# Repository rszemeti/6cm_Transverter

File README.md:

# 6cm_Transverter
Transverter for the 6cm band

Filters done in Sonnet Lite
PCB In Eagle

RF Board is setup for Rogers RO4003C, 0.508mm
DC Board is any FR4

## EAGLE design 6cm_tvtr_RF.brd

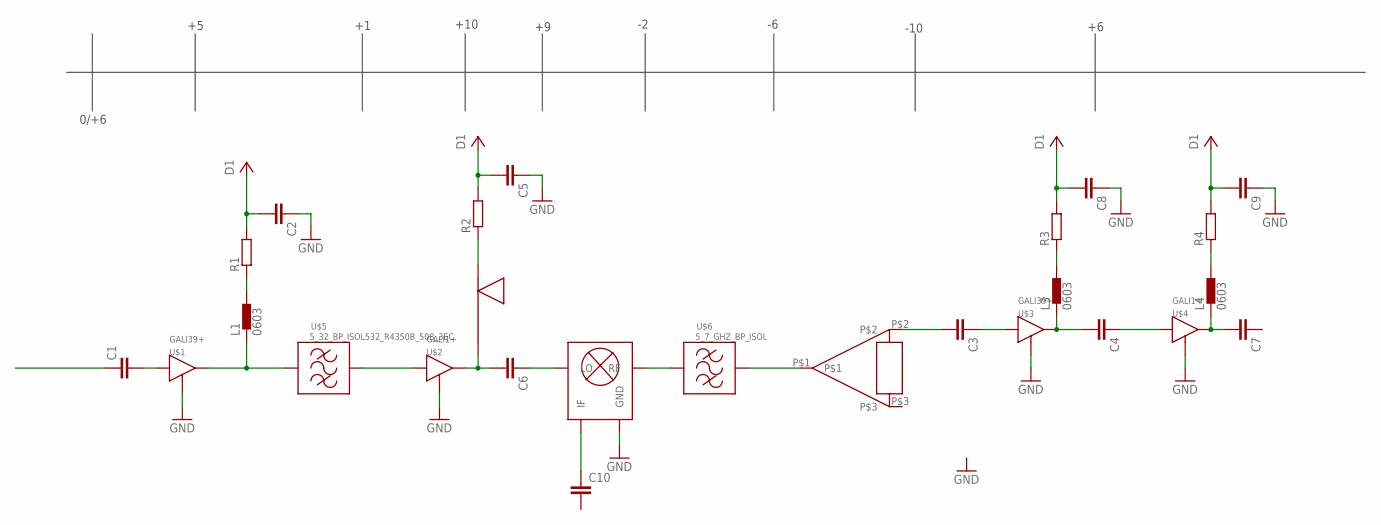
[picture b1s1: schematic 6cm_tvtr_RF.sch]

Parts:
C1, C2, C3, C4, C5, C6, C7, C8, C9, C10: C-EUC0603K; C0603K
L1, L3, L4: 0603
R1, R2, R3, R4: R-EU_R0603; R0603
U$1, U$3: GALI39+; DF782
U$2, U$4: GALI1+; DF782
U$5: 5_32_BP_ISOL532_R4350B_508_3EC; 532_R4350B_508_3EC
U$6: 5_7_GHZ_BP_ISOL; 576_R403C_508_5TH
U$7: 576_WILK
U$8: MDB-73H+; DG1847
U$9: STUB; 5.3_R4350B_508_STUB_90

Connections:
D1: C5.2, C8.2, C9.2, R2.2, R3.2, R4.2
GND: C2.1, C5.1, C8.1, C9.1, U$1.P$2 (GND), U$1.P$4 (GND), U$1.P$5 (GND), U$1.P$6 (GND), U$1.P$7 (GND), U$1.P$8 (GND), U$2.P$2 (GND), U$2.P$4 (GND), U$2.P$5 (GND), U$2.P$6 (GND), U$2.P$7 (GND), U$2.P$8 (GND), U$3.P$2 (GND), U$3.P$4 (GND), U$3.P$5 (GND), U$3.P$6 (GND), U$3.P$7 (GND), U$3.P$8 (GND), U$4.P$2 (GND), U$4.P$4 (GND), U$4.P$5 (GND), U$4.P$6 (GND), U$4.P$7 (GND), U$4.P$8 (GND), U$8.P$2 (GND), U$8.P$4 (GND), U$8.P$8 (GND), U$8.P$10 (GND), U$8.P$15 (GND), U$8.P$17 (GND), U$8.PAD1 (GND), U$8.PAD2 (GND), U$8.PAD3 (GND), U$8.PAD4 (GND)
unnamed: C1.2, U$1.P$1 (IN)
unnamed: R2.1, U$9.DC
unnamed: C6.2, U$2.P$3 (OUT), U$9.RF (RF_END)
unnamed: L1.P$2 (2), R1.1
unnamed: L1.P$1 (1), U$1.P$3 (OUT), U$5.P$1
unnamed: U$2.P$1 (IN), U$5.P$2
unnamed: U$6.P$2, U$7.P$1
unnamed: C6.1, U$8.P$16 (LO)
unnamed: C3.2, U$7.P$2
unnamed: U$6.P$1, U$8.P$3 (RF)
unnamed: C3.1, U$3.P$1 (IN)
unnamed: C4.2, L3.P$1 (1), U$3.P$3 (OUT)
unnamed: C4.1, U$4.P$1 (IN)
unnamed: C7.2, L4.P$1 (1), U$4.P$3 (OUT)
unnamed: L3.P$2 (2), R3.1
unnamed: L4.P$2 (2), R4.1
unnamed: C10.1, U$8.P$9 (IF)
VCC: C2.2, R1.2

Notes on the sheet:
0/+6
+10
-10

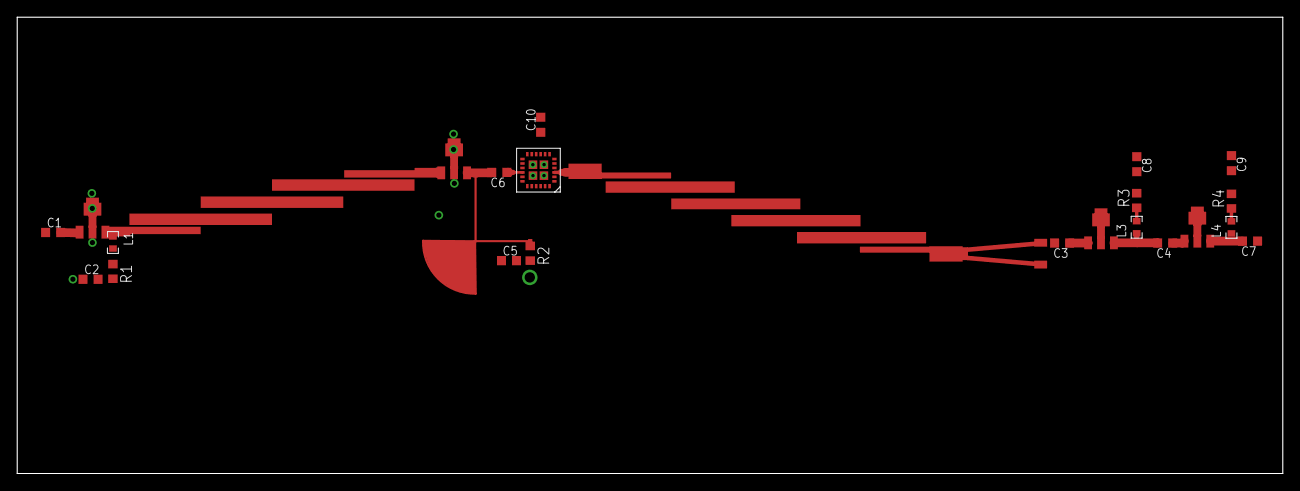
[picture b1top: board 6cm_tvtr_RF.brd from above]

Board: 2 copper layers, 147.0 x 53.0 mm, 26 parts (0 on the bottom side), 20 nets.

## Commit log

2023-08-28 Filters
    Filters, initial commit
2023-08-28 PCB Initial
2023-08-29 matching
2023-08-29 Q1 input match
2023-08-29 Output Match
2023-08-29 misc
2023-08-29 matlab ... meh
    gamma_S appears to have the "wrong" sign on the angle ..
2023-08-31 layout with GAL1+ etc
2023-09-12 Progress ...
2023-09-17 Calcs for layout
